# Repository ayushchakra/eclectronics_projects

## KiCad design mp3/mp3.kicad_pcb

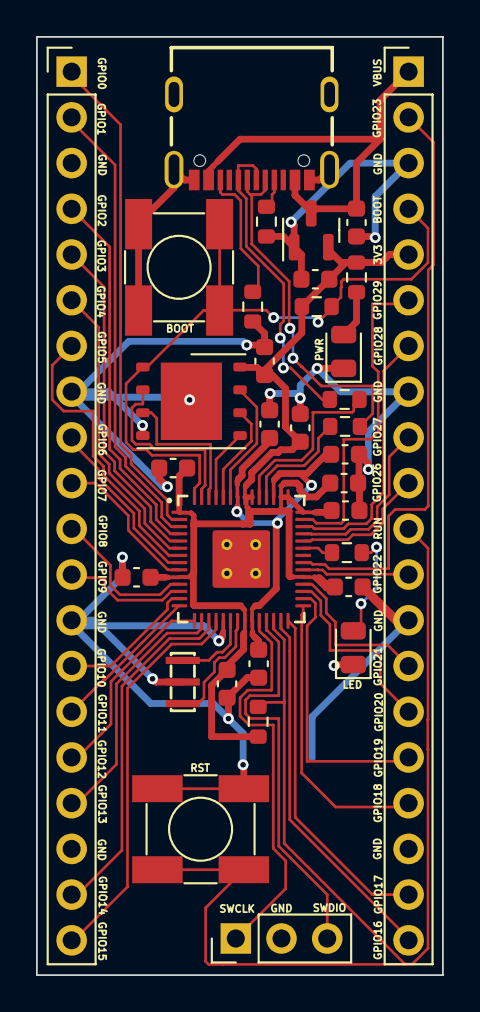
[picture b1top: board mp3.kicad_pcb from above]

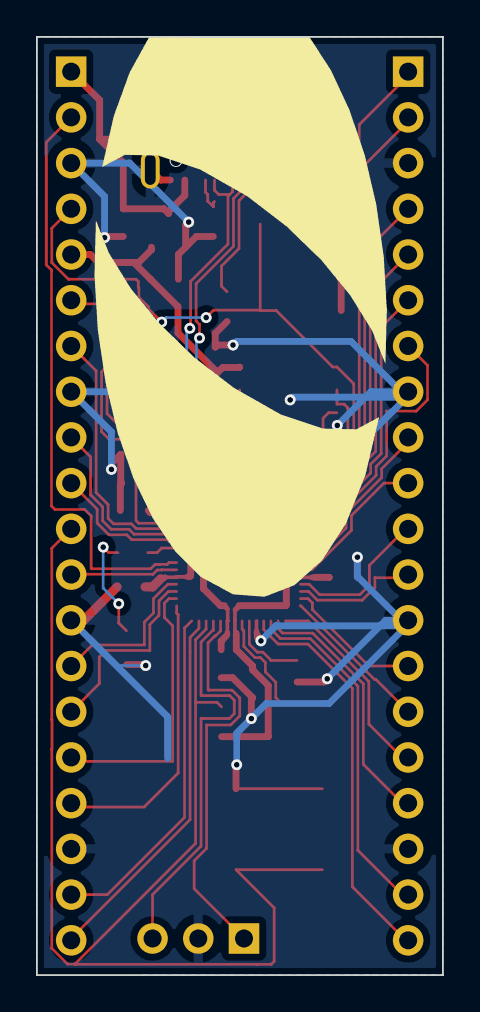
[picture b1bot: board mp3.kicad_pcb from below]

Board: 2 copper layers, 22.6 x 52.1 mm, 35 parts (2 on the bottom side), 52 nets.

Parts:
BOOT: BOOT; TL3301AFxxxxJ
C1, C2, C3, C4, C5, C6, C7, C10, C11: 0.1µF; C_0603_1608Metric
C8, C9: 1µF; C_0603_1608Metric
C12, C13: 10µF; C_0603_1608Metric
J1: USB4105-GF-A
J2: LEFT; PinHeader_1x20_P2.54mm_Vertical
J3: DEBUG; PinHeader_1x03_P2.54mm_Vertical
J4: RIGHT; PinHeader_1x20_P2.54mm_Vertical
LED: LED; LED_0805_2012Metric
OlinLogoTruncated_0.6in, OlinLogoTruncated_0.6in#2: G***; OlinLogoTruncated_0.6in
PWR: PWR; LED_0805_2012Metric
R1, R2, R3, R4: 5.1K; R_0603_1608Metric
R5, R6: 27Ω; R_0603_1608Metric
R7, R8: 1K; R_0603_1608Metric
RST: RST; TL3301AFxxxxJ
U1: W25Q128JV; WSON-8-1EP_6x5mm_P1.27mm_EP3.4x4.3mm
U2: RP2040
U3: MCP1702T-3302E_CB; SOT-23
Y1: 12MHz; CSTNE

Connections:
+3V3: C1.2, C2.1, C3.1, C4.1, C5.1, C6.1, C7.1, C8.1, C13.1, J4.5, R2.2, R3.2, R8.1, U1.8 (VDD), U2.1 (IOVDD), U2.10 (IOVDD), U2.22 (IOVDD), U2.33 (IOVDD), U2.42 (IOVDD), U2.43 (ADC_AVDD), U2.44 (VREG_VIN), U2.48 (USB_VDD), U2.49 (IOVDD), U3.2 (VOUT)
/BOOT: BOOT.2, J4.4, R3.1, U1.1 (~CS), U2.56 (~QSPI_CS)
/GPIO0: J2.1, U2.2 (GPIO0)
/GPIO1: J2.2, U2.3 (GPIO1)
/GPIO2: J2.4, U2.4 (GPIO2)
/GPIO3: J2.5, U2.5 (GPIO3)
/GPIO4: J2.6, U2.6 (GPIO4)
/GPIO5: J2.7, U2.7 (GPIO5)
/GPIO6: J2.9, U2.8 (GPIO6)
/GPIO7: J2.10, U2.9 (GPIO7)
/GPIO8: J2.11, U2.11 (GPIO8)
/GPIO9: J2.12, U2.12 (GPIO9)
/GPIO10: J2.14, U2.13 (GPIO10)
/GPIO11: J2.15, U2.14 (GPIO11)
/GPIO12: J2.16, U2.15 (GPIO12)
/GPIO13: J2.17, U2.16 (GPIO13)
/GPIO14: J2.19, U2.17 (GPIO14)
/GPIO15: J2.20, U2.18 (GPIO15)
/GPIO16: J4.20, U2.27 (GPIO16)
/GPIO17: J4.19, U2.28 (GPIO17)
/GPIO18: J4.17, U2.29 (GPIO18)
/GPIO19: J4.16, U2.30 (GPIO19)
/GPIO20: J4.15, U2.31 (GPIO20)
/GPIO21: J4.14, U2.32 (GPIO21)
/GPIO22: J4.12, U2.34 (GPIO22)
/GPIO23: J4.2, U2.35 (GPIO23)
/GPIO25: R7.1, U2.37 (GPIO25)
/GPIO26: J4.10, U2.38 (GPIO26/ADC0)
/GPIO27: J4.9, U2.39 (GPIO27/ADC1)
/GPIO28: J4.7, U2.40 (GPIO28/ADC2)
/GPIO29: J4.6, U2.41 (GPIO29/ADC3)
/RUN: J4.11, R2.1, RST.2, U2.26 (RUN)
/SWCLK: J3.1, U2.24 (SWCLK)
/SWDIO: J3.3, U2.25 (SWDIO)
/VBUS: C12.2, J1.A4B9 (VBUS), J1.B4A9 (VBUS), J4.1, U3.3 (VIN)
GND: BOOT.1, C1.1, C2.2, C3.2, C4.2, C5.2, C6.2, C7.2, C8.2, C9.2, C10.2, C11.2, C12.1, C13.2, J1.A1B12 (GND), J1.B1A12 (GND), J1.S1 (SHELL), J1.S2 (SHELL), J1.S3 (SHELL), J1.S4 (SHELL), J2.3, J2.8, J2.13, J2.18, J3.2, J4.3, J4.8, J4.13, J4.18, LED.1 (K), PWR.1 (K), R1.2, R4.2, RST.1, U1.4 (GND), U1.9 (EP), U2.19 (TESTEN), U2.57 (GND), U3.1 (GND), Y1.2
unnamed: C9.1, C10.1, C11.1, U2.23 (DVDD), U2.45 (VREG_VOUT), U2.50 (DVDD)
unnamed: LED.2 (A), R7.2
unnamed: PWR.2 (A), R8.2
unnamed: J1.A5 (CC1), R4.1
unnamed: J1.A6 (D+), J1.B6 (D+), R6.1
unnamed: J1.A7 (D-), J1.B7 (D-), R5.1
unnamed: J1.B5 (CC2), R1.1
unnamed: R5.2, U2.46 (USB_D-)
unnamed: R6.2, U2.47 (USB_D+)
unnamed: U1.2 (DO/IO1), U2.55 (QSPI_SD1)
unnamed: U1.3 (~WP/IO2), U2.54 (QSPI_SD2)
unnamed: U1.5 (DI/IO0), U2.53 (QSPI_SD0)
unnamed: U1.6 (SCK), U2.52 (QSPI_SCLK)
unnamed: U1.7 (~HOLD/IO3), U2.51 (QSPI_SD3)
unnamed: U2.20 (XIN), Y1.1
unnamed: U2.21 (XOUT), Y1.3

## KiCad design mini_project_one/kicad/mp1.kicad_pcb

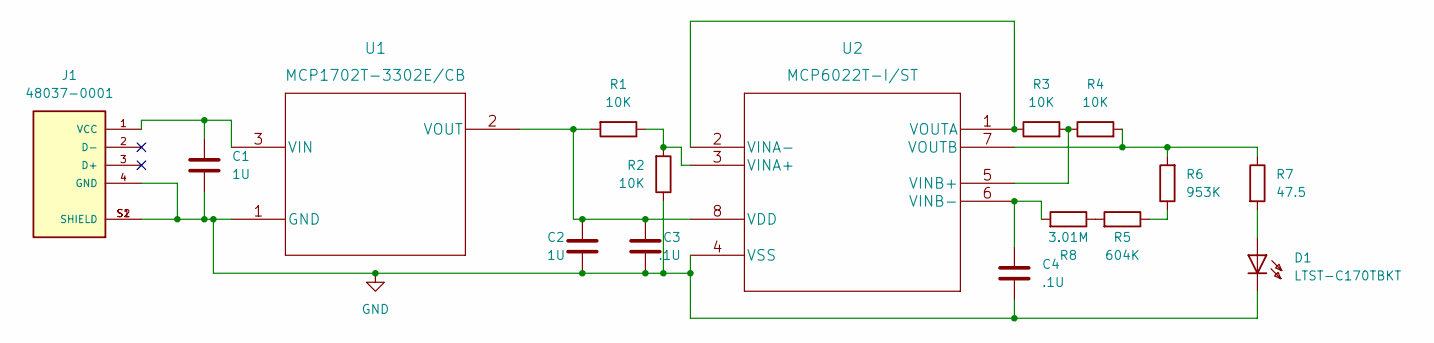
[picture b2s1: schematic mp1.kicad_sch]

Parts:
C1, C2: 1U; C_0603_1608Metric_Pad1.08x0.95mm_HandSolder
C3, C4: .1U; C_0603_1608Metric_Pad1.08x0.95mm_HandSolder
D1: LTST-C170TBKT; 160-1579-1-ND
J1: 48037-0001; MOLEX_48037-0001; PARTREV D
R1, R2, R3, R4: 10K; R_0603_1608Metric_Pad0.98x0.95mm_HandSolder
R5: 604K; R_0603_1608Metric_Pad0.98x0.95mm_HandSolder
R6: 953K; R_0603_1608Metric_Pad0.98x0.95mm_HandSolder
R7: 47.5; R_0603_1608Metric_Pad0.98x0.95mm_HandSolder
R8: 3.01M; R_0603_1608Metric_Pad0.98x0.95mm_HandSolder
U1: MCP1702T-3302E/CB; MCP1702T-3302E&slash_CB
U2: MCP6022T-I/ST; MCP6022T-I&slash_ST

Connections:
GND: C1.2, C2.2, C3.2, C4.1, D1.-, J1.4 (GND), J1.S1 (SHIELD), J1.S2 (SHIELD), R2.1, U1.1 (GND), U2.4 (VSS)
unnamed: C1.1, J1.1 (VCC), U1.3 (VIN)
unnamed: C2.1, C3.1, R1.2, U1.2 (VOUT), U2.8 (VDD)
unnamed: C4.2, R8.2, U2.6 (VINB-)
unnamed: D1.+, R7.2
unnamed: R1.1, R2.2, U2.3 (VINA+)
unnamed: R3.1, U2.1 (VOUTA), U2.2 (VINA-)
unnamed: R3.2, R4.1, U2.5 (VINB+)
unnamed: R4.2, R6.2, R7.1, U2.7 (VOUTB)
unnamed: R5.1, R6.1
unnamed: R5.2, R8.1

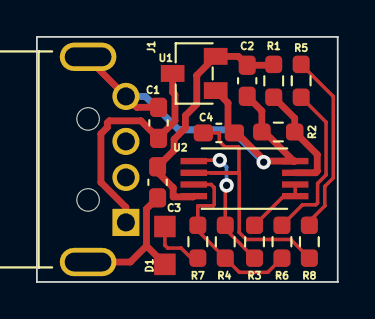
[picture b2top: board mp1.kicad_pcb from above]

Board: 2 copper layers, 16.7 x 13.6 mm, 16 parts (0 on the bottom side), 11 nets.

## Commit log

2022-09-15 added kicad files for mp1
2022-09-15 added ltspice model, data, and python analysis
2022-09-15 added gitignore and updated parts libraries
2022-09-15 added downloaded schematic and footprints
2022-09-15 updated ltspice analysis and uploaded files
2022-09-15 added cache to gitignore
2022-09-16 updated design and added bom
2022-09-16 updated courtyards of downloaded parts
2022-09-16 cleaned up ltspice files
2022-09-16 added bom for layout
2022-09-16 added report to repo
2022-09-16 fixed full path errors for kicad footprints and symbols
2022-10-04 added brad's eclectronics folder
2022-10-04 moved gitignore and added first pass of rp2040 dev board
2022-10-04 added olin logo to pcb
2022-10-06 second revision of rp devboard
2022-12-26 --wip-- [skip ci]

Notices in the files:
parts and their libraries:
Copyright 2021 Accelerated Designs. All rights reserved.
